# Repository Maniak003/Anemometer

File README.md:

<!DOCTYPE html>
<html lang="en" data-color-mode="auto" data-light-theme="light" data-dark-theme="dark">
  <head>
    <meta charset="utf-8">
  </head>
    <body class="logged-in env-production page-responsive page-blob" style="word-wrap: break-word;">
      <p> UltraSonic Anemometer.<br><b>Temperature instability was found. I'm trying to solve a problem. </p>

      <a href="https://github.com/Maniak003/Anemometer/wiki/Description" rel="nofollow">Description</a>
    </body>
</html>

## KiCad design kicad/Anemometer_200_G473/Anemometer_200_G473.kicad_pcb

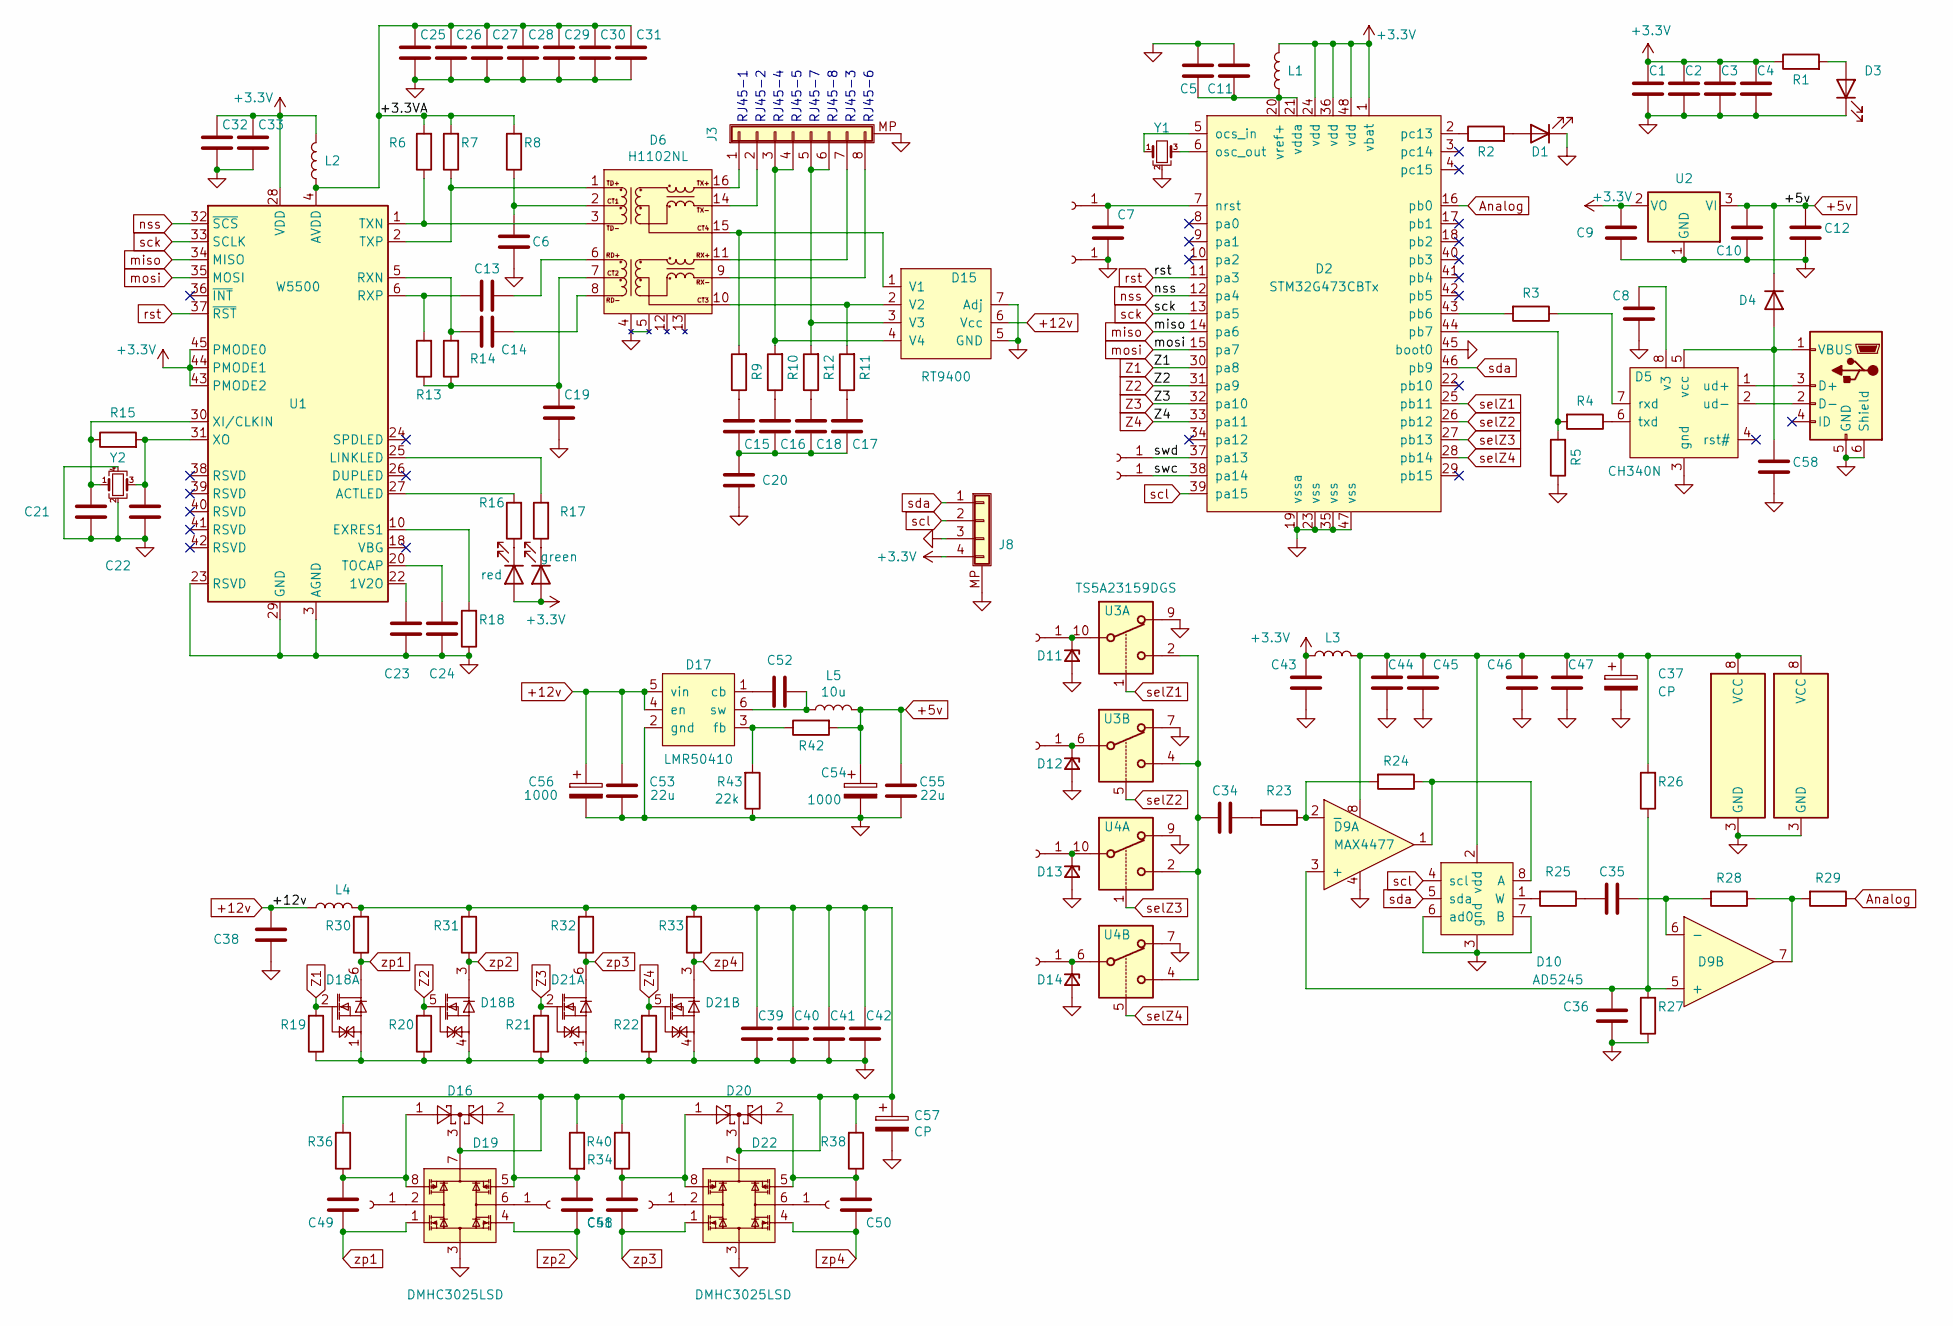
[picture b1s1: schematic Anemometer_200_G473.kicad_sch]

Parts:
C1, C8, C9, C38, C43, C44, C45, C46, C47: C; C_0603_1608Metric
C2, C3, C4, C5, C10, C11, C12, C39, C40, C41, C42, C58: C; C_0805_2012Metric
C6, C25, C26, C27, C28, C29, C30, C31, C32, C33: 22n; C_0402_1005Metric
C7: C; C_0402_1005Metric
C13, C14, C15, C16, C17, C18, C36: 6.8n; C_0402_1005Metric
C19, C23: 10n; C_0402_1005Metric
C20: 10n; C_1206_3216Metric
C21, C22: 10; C_0402_1005Metric
C24, C34, C35: 4.7u; C_0402_1005Metric
C37, C57: CP; CP_EIA-7343-40_Kemet-Y_Pad2.25x2.55mm_HandSolder
C48, C49, C50, C51, C52: 85n; C_0603_1608Metric
C53, C55: 22u; C_0805_2012Metric
C54, C56: 1000; CP_EIA-7343-40_Kemet-Y_Pad2.25x2.55mm_HandSolder
D1, D3: LED; LED_0603_1608Metric
D2: STM32G473CBTx; LQFP-48_7x7mm_P0.5mm
D4: D; D_MiniMELF
D5: CH340N; SOP-8_3.9x4.9mm_P1.27mm
D6: H1102NL; H1102N
D7: red; LED_0603_1608Metric
D8: green; LED_0603_1608Metric
D9: MAX4477; MSOP-8_3x3mm_P0.65mm
D10: AD5245; MSOP-8_3x3mm_P0.65mm
D11, D12, D13, D14: D_Zener_Small; D_SOD-123
D15: RT9400; TR9400
D16, D20: BAT54C; SOT-23
D17: LMR50410; SOT-23-6
D18, D21: DMN5L06DWK-7; SOT-363_SC-70-6
D19, D22: DMHC3025LSD; SO-8_5.3x6.2mm_P1.27mm
J1, J2, J4, J13, J15, J16, J17, J20, J21, J22, J23, J24: Conn_01x01_Female; conn_mini
J3: Conn_01x08_Shielded; JST_GH_BM08B-GHS-TBT_1x08-1MP_P1.25mm_Vertical
J8: Conn_01x04_Shielded; JST_SH_BM04B-SRSS-TB_1x04-1MP_P1.00mm_Vertical
J11: USB_B_Micro; USB_Micro-B_Molex_47346-0001
L1: L; L_0805_2012Metric
L2, L4: 10u; L_0805_2012Metric
L3: 47u; L_0805_2012Metric
L5: 10u; L_Bourns_SRP7028A_7.3x6.6mm
R1, R2, R3, R4, R5, R23, R24, R25, R28, R29: R; R_0603_1608Metric
R6, R7: 49.9; R_0402_1005Metric
R8: 10; R_0402_1005Metric
R9, R10, R11, R12: 75; R_0402_1005Metric
R13, R14: 82; R_0402_1005Metric
R15: 1M; R_0402_1005Metric
R16, R17: 510; R_0402_1005Metric
R18, R26, R27, R34, R36, R38, R40, R42: 12.4k; R_0402_1005Metric
R19, R20, R21, R22: 100k; R_0402_1005Metric
R30, R31, R32, R33: 100; R_0402_1005Metric
R43: 22k; R_0402_1005Metric
U1: W5500; LQFP-48_7x7mm_P0.5mm
U2: NCP1117-3.3; SOT-223-3_TabPin2
U3, U4: TS5A23159DGS; VSSOP-10_3x3mm_P0.5mm
Y1: 16; Resonator_SMD_muRata_CSTxExxV-3Pin_3.0x1.1mm
Y2: 25MHz; Crystal_SMD_SeikoEpson_FA238-4Pin_3.2x2.5mm

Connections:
+3V3: C1.1, C2.1, C3.1, C4.1, C9.1, C32.1, C33.1, C43.1, D2.1 (vbat), D2.24 (vdd), D2.36 (vdd), D2.48 (vdd), D7.2 (A), D8.2 (A), J8.4, L1.2, L2.2, L3.1, R1.1, U1.28 (VDD), U1.43 (PMODE2), U1.44 (PMODE1), U1.45 (PMODE0), U2.2 (VO)
+5v: C10.1, C12.1, C54.1, C55.2, D4.1 (K), L5.2, R42.2, U2.3 (VI)
+12v: C38.1, C53.2, C56.1, D15.6 (Vcc), D17.4 (en), D17.5 (vin), L4.1
/+3.3VA: C25.1, C26.1, C27.1, C28.1, C29.1, C30.1, C31.1, L2.1, R6.2, R7.2, R8.2, U1.4 (AVDD), U1.8 (AVDD), U1.11 (AVDD), U1.15 (AVDD), U1.17 (AVDD), U1.21 (AVDD)
/swc: D2.38 (pa14), J21.1
/swd: D2.37 (pa13), J20.1
Analog: D2.16 (pb0), R29.1
GND: C1.2, C2.2, C3.2, C4.2, C5.2, C6.2, C7.2, C8.2, C9.2, C10.2, C11.2, C12.2, C19.2, C20.2, C21.2, C22.2, C23.2, C24.2, C25.2, C26.2, C27.2, C28.2, C29.2, C30.2, C31.2, C32.2, C33.2, C36.1, C37.2, C38.2, C39.2, C40.2, C41.2, C42.2, C43.2, C44.2, C45.2, C46.2, C47.2, C53.1, C54.2, C55.1, C56.2, C57.2, C58.2, D1.1 (K), D2.19 (vssa), D2.23 (vss), D2.35 (vss), D2.45 (boot0), D2.47 (vss), D3.1 (K), D5.3 (gnd), D6.4, D6.5, D9.4, D10.3 (gnd), D10.6 (ad0), D10.7 (B), D11.2 (A), D12.2 (A), D13.2 (A), D14.2 (A), D15.5 (GND), D15.7 (Adj), D17.2 (gnd), D18.1, D18.4, D19.3, D21.1, D21.4, D22.3, J3.MP (Shield), J4.1, J8.3, J8.MP (Shield), J11.5 (GND), J11.6 (Shield), R5.1, R18.1, R19.1, R20.1, R21.1, R22.1, R27.1, R43.1, U1.3 (AGND), U1.9 (AGND), U1.14 (AGND), U1.16 (AGND), U1.19 (AGND), U1.23 (RSVD), U1.29 (GND), U1.48 (AGND), U2.1 (GND), U3.3 (GND), U3.7, U3.9, U4.3 (GND), U4.7, U4.9, Y1.2, Y2.2, Y2.4
unnamed: C6.1, D6.2, R8.1
unnamed: C7.1, D2.7 (nrst), J1.1
unnamed: C8.1, D5.8 (v3)
unnamed: C5.1, C11.1, D2.20 (vref+), D2.21 (vdda), L1.1
unnamed: C13.1, D6.6
unnamed: C13.2, R13.2, U1.6 (RXP)
unnamed: C14.1, D6.8
unnamed: C14.2, R14.2, U1.5 (RXN)
unnamed: C15.2, R9.1
unnamed: C16.2, R10.1
unnamed: C18.2, R12.1
unnamed: C19.1, D6.7, R13.1, R14.1
unnamed: C15.1, C16.1, C17.1, C18.1, C20.1
unnamed: C21.1, R15.1, U1.30 (XI/CLKIN), Y2.1
unnamed: C22.1, R15.2, U1.31 (XO), Y2.3
unnamed: C23.1, U1.22 (1V2O)
unnamed: C24.1, U1.20 (TOCAP)
unnamed: C34.1, R23.2
unnamed: C34.2, U3.2, U3.4, U4.2, U4.4
unnamed: C35.1, D9.6 (-), R28.2
unnamed: C35.2, R25.1
unnamed: C36.2, D9.3 (+), D9.5 (+), R26.1, R27.2
unnamed: C37.1, C44.1, C45.1, C46.1, C47.1, D9.8, D10.2 (vdd), L3.2, R26.2, U3.8 (VCC), U4.8 (VCC)
unnamed: C39.1, C40.1, C41.1, C42.1, C57.1, D16.3, D19.7, D20.3, D22.7, L4.2, R30.2, R31.2, R32.2, R33.2, R34.1, R36.2, R38.2, R40.2
unnamed: C48.1, D16.2, D19.5, R34.2
unnamed: C49.1, D16.1, D19.8, R36.1
unnamed: C50.1, D20.2, D22.5, R38.1
unnamed: C51.1, D20.1, D22.8, R40.1
unnamed: C52.1, D17.6 (sw), L5.1
unnamed: C52.2, D17.1 (cb)
unnamed: D1.2 (A), R2.2
unnamed: D2.2 (pc13), R2.1
unnamed: D2.5 (ocs_in), Y1.1
unnamed: D2.6 (osc_out), Y1.3
unnamed: D2.43 (pb6), R3.2
unnamed: D2.44 (pb7), R4.2, R5.2
unnamed: D3.2 (A), R1.2
unnamed: C58.1, D4.2 (A), D5.5 (vcc), J11.1 (VBUS)
unnamed: D5.1 (ud+), J11.3 (D+)
unnamed: D5.2 (ud-), J11.2 (D-)
unnamed: D5.6 (txd), R4.1
unnamed: D5.7 (rxd), R3.1
unnamed: D6.9, J3.8
unnamed: D6.11, J3.7
unnamed: D6.14, J3.2
unnamed: D6.16, J3.1
unnamed: D9.2 (-), R23.1, R24.2
unnamed: D9.7, R28.1, R29.2
unnamed: D10.1 (W), R25.2
unnamed: D9.1, D10.8 (A), R24.1
unnamed: D11.1 (K), J17.1, U3.10
unnamed: D12.1 (K), J22.1, U3.6
unnamed: D13.1 (K), J23.1, U4.10
unnamed: D14.1 (K), J24.1, U4.6
unnamed: D6.15, D15.1 (V1), R9.2
unnamed: D6.10, D15.2 (V2), R11.2
unnamed: D15.3 (V3), J3.5, J3.6, R12.2
unnamed: D15.4 (V4), J3.3, J3.4, R10.2
unnamed: D17.3 (fb), R42.1, R43.2
unnamed: D19.6, J2.1
unnamed: D22.2, J13.1
unnamed: D19.2, J15.1
unnamed: D22.6, J16.1
unnamed: D6.3, R6.1, U1.1 (TXN)
unnamed: D6.1, R7.1, U1.2 (TXP)
unnamed: C17.2, R11.1
unnamed: D7.1 (K), R16.1
unnamed: D8.1 (K), R17.1
unnamed: R18.2, U1.10 (EXRES1)
unnamed: R17.2, U1.25 (LINKLED)
unnamed: R16.2, U1.27 (ACTLED)
Z1: D2.30 (pa8), D18.2, R19.2
Z2: D2.31 (pa9), D18.5, R20.2
Z3: D2.32 (pa10), D21.2, R21.2
Z4: D2.33 (pa11), D21.5, R22.2
miso: D2.14 (pa6), U1.34 (MISO)
mosi: D2.15 (pa7), U1.35 (MOSI)
nss: D2.12 (pa4), U1.32 (~SCS)
rst: D2.11 (pa3), U1.37 (~RST)
sck: D2.13 (pa5), U1.33 (SCLK)
scl: D2.39 (pa15), D10.4 (scl), J8.2
sda: D2.46 (pb9), D10.5 (sda), J8.1
selZ1: D2.25 (pb11), U3.1
selZ2: D2.26 (pb12), U3.5
selZ3: D2.27 (pb13), U4.1
selZ4: D2.28 (pb14), U4.5
zp1: C49.2, D18.6, D19.1, R30.1
zp2: C48.2, D18.3, D19.4, R31.1
zp3: C51.2, D21.6, D22.1, R32.1
zp4: C50.2, D21.3, D22.4, R33.1

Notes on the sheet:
RJ45-1
RJ45-3
RJ45-2
RJ45-6
RJ45-8
RJ45-5
RJ45-4
RJ45-7

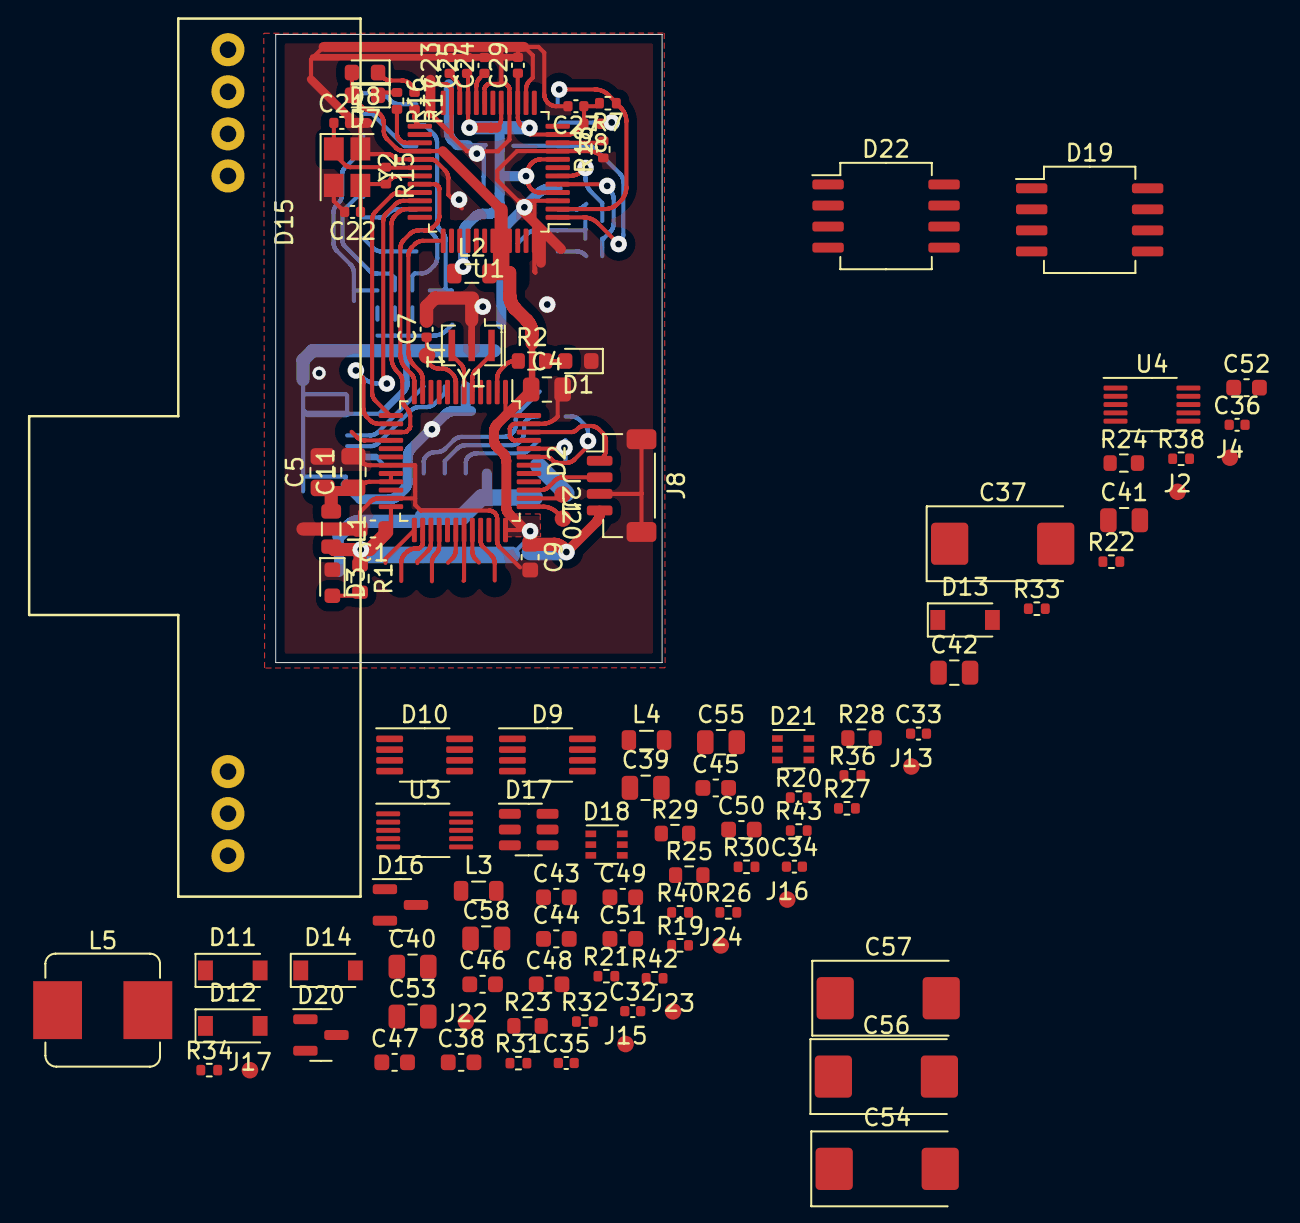
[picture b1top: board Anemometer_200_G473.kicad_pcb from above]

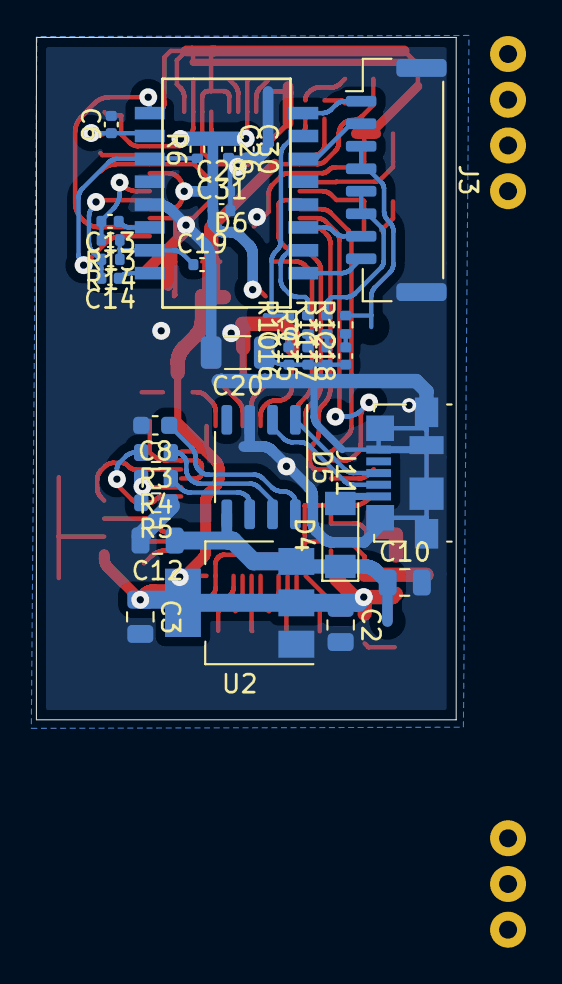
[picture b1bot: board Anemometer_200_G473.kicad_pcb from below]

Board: 2 copper layers, 23.3 x 37.9 mm, 145 parts (34 on the bottom side), 98 nets.

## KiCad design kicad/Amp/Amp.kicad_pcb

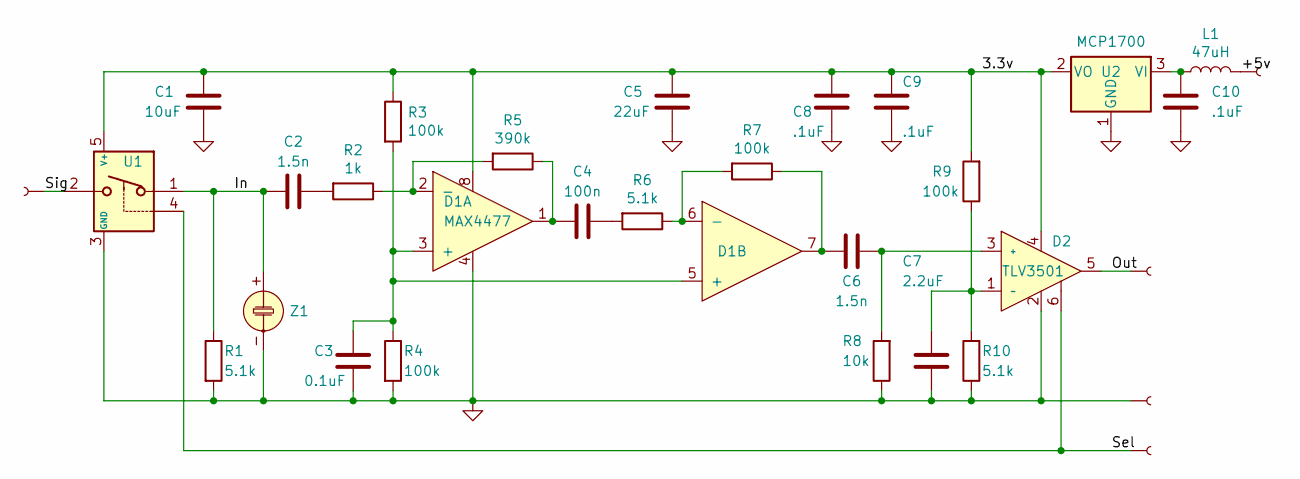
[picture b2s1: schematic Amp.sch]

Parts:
C1: 10uF; C_0603_1608Metric
C2, C6: 1.5n; C_0402_1005Metric
C3: 0.1uF; C_0402_1005Metric
C4: 100n; C_0402_1005Metric
C5: 22uF; C_0805_2012Metric
C7: 2.2uF; C_0402_1005Metric
C8, C9, C10: .1uF; C_0603_1608Metric
D1: MAX4477; MSOP-8_3x3mm_P0.65mm
D2: TLV3501; SOT-23-6
J1, J2, J3, J4, J5: Conn; SMD-CONN
L1: 47uH; L_0805_2012Metric
R1, R6, R10: 5.1k; R_0402_1005Metric
R2: 1k; R_0402_1005Metric
R3, R4, R7, R9: 100k; R_0402_1005Metric
R5: 390k; R_0402_1005Metric
R8: 10k; R_0402_1005Metric
U1: TS5A3166DBVR; SOT-23-5
U2: MCP1700; SOT-23
Z1: MCUSD18A40B12RS

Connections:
/3.3v: C1.1, C5.1, C8.1, C9.1, D1.8, D2.4, R3.1, R9.2, U1.5 (V+), U2.2 (VO)
/+5v: J5.1, L1.2
/In: C2.2, R1.1, U1.1, Z1.+
/Out: D2.5, J2.1
/Sel: D2.6, J4.1, U1.4
/Sig: J1.1, U1.2
GND: C1.2, C3.2, C5.2, C7.2, C8.2, C9.2, C10.2, D1.4, D2.2, J3.1, R1.2, R4.2, R8.1, R10.1, U1.3 (GND), U2.1 (GND), Z1.-
unnamed: C2.1, R2.2
unnamed: C3.1, D1.3 (+), D1.5 (+), R3.2, R4.1
unnamed: C4.1, R6.2
unnamed: C4.2, D1.1, R5.1
unnamed: C6.1, D2.3 (+), R8.2
unnamed: C6.2, D1.7, R7.1
unnamed: C7.1, D2.1 (-), R9.1, R10.2
unnamed: C10.1, L1.1, U2.3 (VI)
unnamed: D1.2 (-), R2.1, R5.2
unnamed: D1.6 (-), R6.1, R7.2

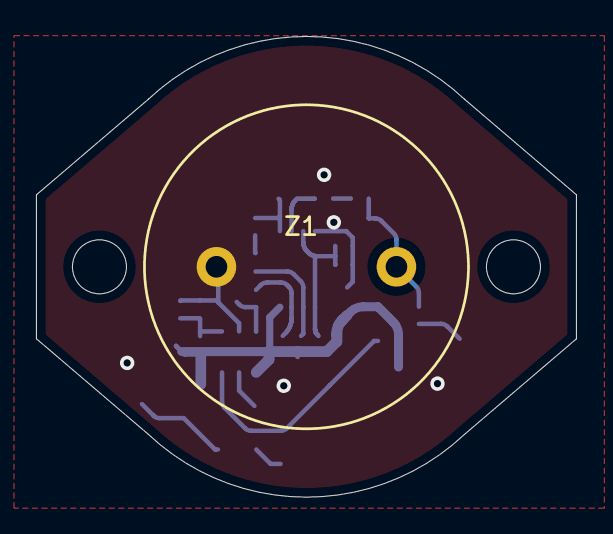
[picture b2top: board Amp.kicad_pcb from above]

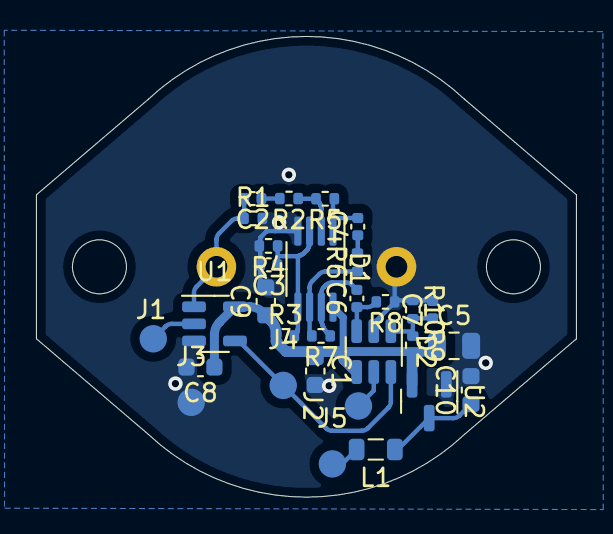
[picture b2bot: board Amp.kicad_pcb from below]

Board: 2 copper layers, 30.0 x 25.6 mm, 31 parts (30 on the bottom side), 17 nets.

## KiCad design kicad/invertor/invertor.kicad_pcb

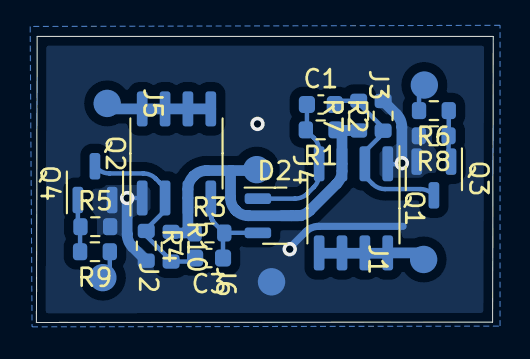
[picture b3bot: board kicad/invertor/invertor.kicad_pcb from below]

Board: 2 copper layers, 25.4 x 15.9 mm, 23 parts (23 on the bottom side), 12 nets.

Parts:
C1, C3: 82nF; C_0603_1608Metric
D2: BAT54C; SOT-23
J1, J2, J3, J4, J5, J6: Conn; SMD-CONN
Q1, Q2: IRF7343PBF; SOIC-8_3.9x4.9mm_P1.27mm
Q3, Q4: IRLML6344; SOT-23
R1, R2, R3, R4, R5, R8: 100k; R_0603_1608Metric
R6, R9: 10; R_0603_1608Metric
R7, R10: 100; R_0603_1608Metric

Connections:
/+12v: D2.3, J4.1, Q1.3 (1), Q2.3 (1), R1.1, R3.1, R7.1, R10.1
/Z1: J2.1, R9.1
/Z2: J3.1, R6.2
GND: J6.1, Q1.1 (S), Q2.1 (S), Q3.2 (S), Q4.2 (S), R2.2, R4.2, R5.2, R8.2
unnamed: C1.1, D2.1, Q1.4 (G), R1.2
unnamed: C1.2, Q1.2 (G), Q3.3 (D), R2.1, R7.2
unnamed: C3.1, D2.2, Q2.4 (G), R3.2
unnamed: C3.2, Q2.2 (G), Q4.3 (D), R4.1, R10.2
unnamed: J1.1, Q1.5 (D), Q1.6 (D), Q1.7 (D), Q1.8 (D)
unnamed: J5.1, Q2.5 (D), Q2.6 (D), Q2.7 (D), Q2.8 (D)
unnamed: Q3.1 (G), R6.1, R8.1
unnamed: Q4.1 (G), R5.1, R9.2

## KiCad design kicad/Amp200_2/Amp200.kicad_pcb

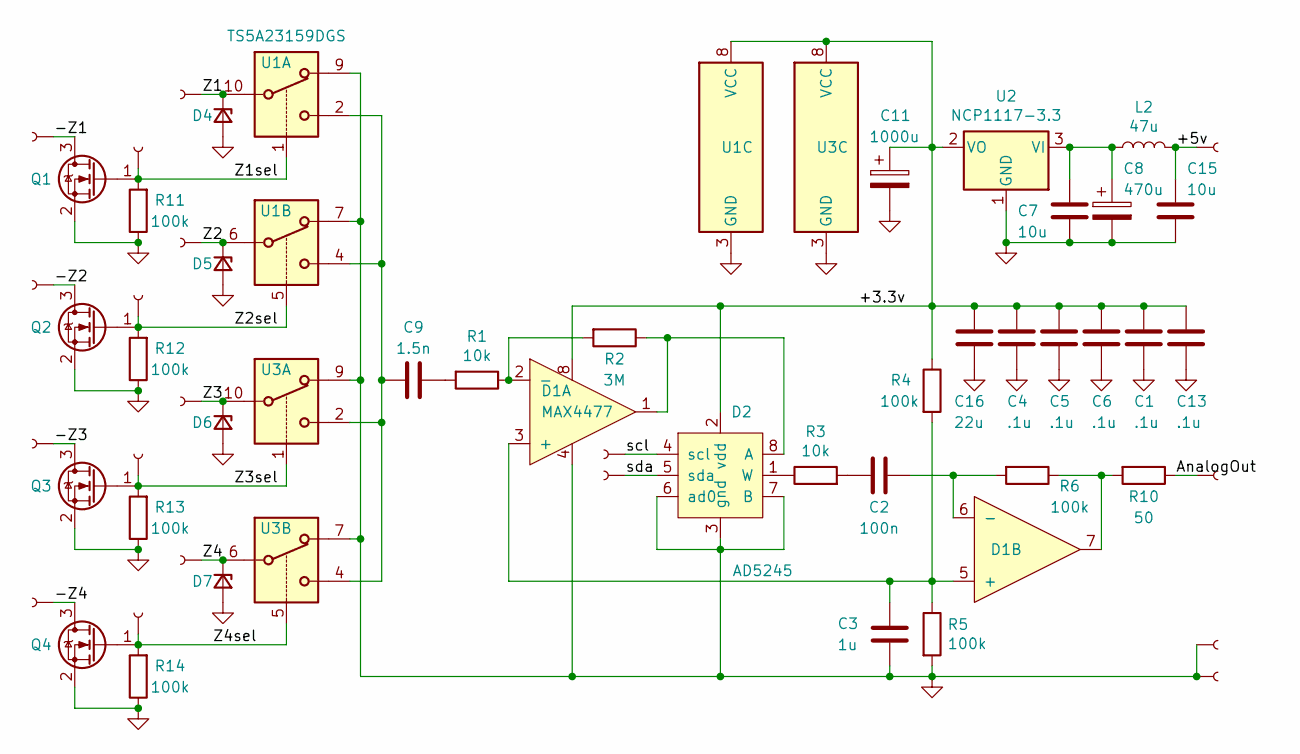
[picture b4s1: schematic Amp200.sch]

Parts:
C1, C4, C5, C6, C13: .1u; C_0805_2012Metric
C2: 100n; C_0603_1608Metric
C3: 1u; C_0603_1608Metric
C7, C15: 10u; C_0805_2012Metric
C8: 470u; CP_EIA-6032-28_Kemet-C
C9: 1.5n; C_0603_1608Metric
C11: 1000u; CP_EIA-6032-28_Kemet-C
C16: 22u; C_0805_2012Metric
D1: MAX4477; MSOP-8_3x3mm_P0.65mm
D2: AD5245; SOT-23-8
D4, D5, D6, D7: BZ55C2V7; D_MiniMELF
J1, J2, J3, J4, J5, J7, J8, J9, J10, J11, J12, J13, J14, J15, J16, J17, J18, J19: Conn; SMD-CONN
L2: 47u; L_0805_2012Metric
Q1, Q2, Q3, Q4: Q_NMOS_GSD; SOT-23
R1, R3: 10k; R_0603_1608Metric
R2: 3M; R_0603_1608Metric
R4, R5, R6, R11, R12, R13, R14: 100k; R_0603_1608Metric
R10: 50; R_0603_1608Metric
U1, U3: TS5A23159DGS; VSSOP-10_3x3mm_P0.5mm
U2: NCP1117-3.3; SOT-223-3_TabPin2

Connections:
/+3.3v: C1.1, C4.1, C5.1, C6.1, C11.1, C13.1, C16.1, D1.8, D2.2 (vdd), R4.1, U1.8 (VCC), U2.2 (VO), U3.8 (VCC)
/+5v: C15.1, J9.1, L2.2
/-Z1: J4.1, Q1.3 (D)
/-Z2: J17.1, Q2.3 (D)
/-Z3: J14.1, Q3.3 (D)
/-Z4: J18.1, Q4.3 (D)
/AnalogOut: J5.1, R10.1
/Z1: D4.1 (K), J1.1, U1.10
/Z1sel: J7.1, Q1.1 (G), R11.2, U1.1
/Z2: D5.1 (K), J11.1, U1.6
/Z2sel: J12.1, Q2.1 (G), R12.2, U1.5
/Z3: D6.1 (K), J13.1, U3.10
/Z3sel: J19.1, Q3.1 (G), R13.2, U3.1
/Z4: D7.1 (K), J15.1, U3.6
/Z4sel: J16.1, Q4.1 (G), R14.2, U3.5
/scl: D2.4 (scl), J2.1
/sda: D2.5 (sda), J3.1
GND: C1.2, C3.2, C4.2, C5.2, C6.2, C7.2, C8.2, C11.2, C13.2, C15.2, C16.2, D1.4, D2.3 (gnd), D2.6 (ad0), D2.7 (B), D4.2 (A), D5.2 (A), D6.2 (A), D7.2 (A), J8.1, J10.1, Q1.2 (S), Q2.2 (S), Q3.2 (S), Q4.2 (S), R5.2, R11.1, R12.1, R13.1, R14.1, U1.3 (GND), U1.7, U1.9, U2.1 (GND), U3.3 (GND), U3.7, U3.9
unnamed: C2.1, D1.6 (-), R6.2
unnamed: C2.2, R3.2
unnamed: C3.1, D1.3 (+), D1.5 (+), R4.2, R5.1
unnamed: C7.1, C8.1, L2.1, U2.3 (VI)
unnamed: C9.1, R1.2
unnamed: C9.2, U1.2, U1.4, U3.2, U3.4
unnamed: D1.1, D2.8 (A), R2.1
unnamed: D1.2 (-), R1.1, R2.2
unnamed: D1.7, R6.1, R10.2
unnamed: D2.1 (W), R3.1

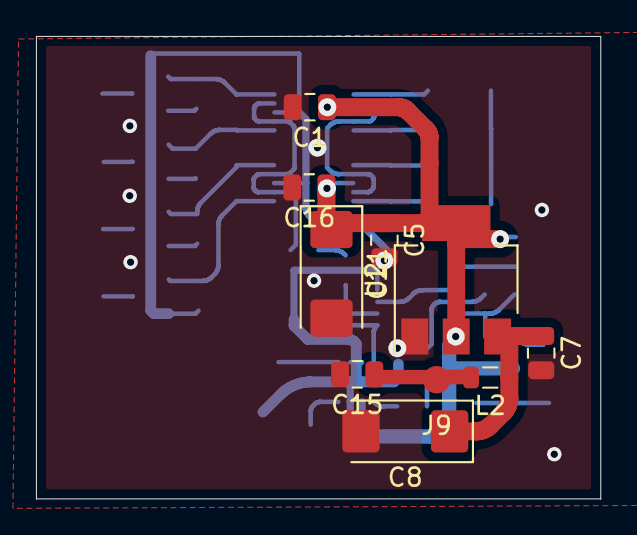
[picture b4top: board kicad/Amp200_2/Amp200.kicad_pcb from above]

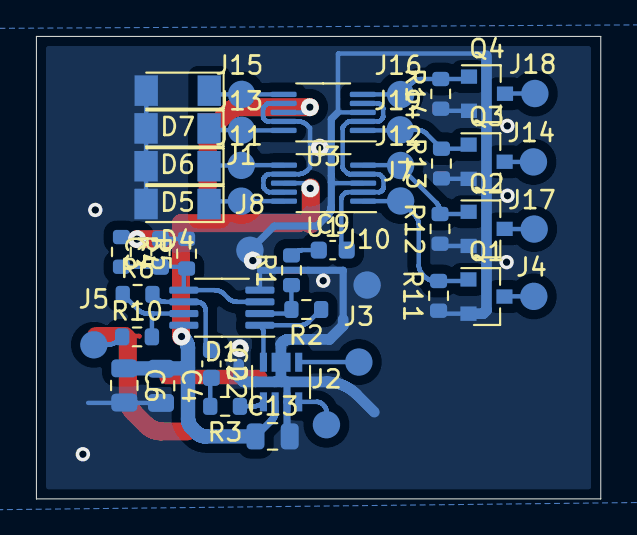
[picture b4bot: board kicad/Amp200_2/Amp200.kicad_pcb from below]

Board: 2 copper layers, 31.4 x 25.7 mm, 56 parts (46 on the bottom side), 28 nets.

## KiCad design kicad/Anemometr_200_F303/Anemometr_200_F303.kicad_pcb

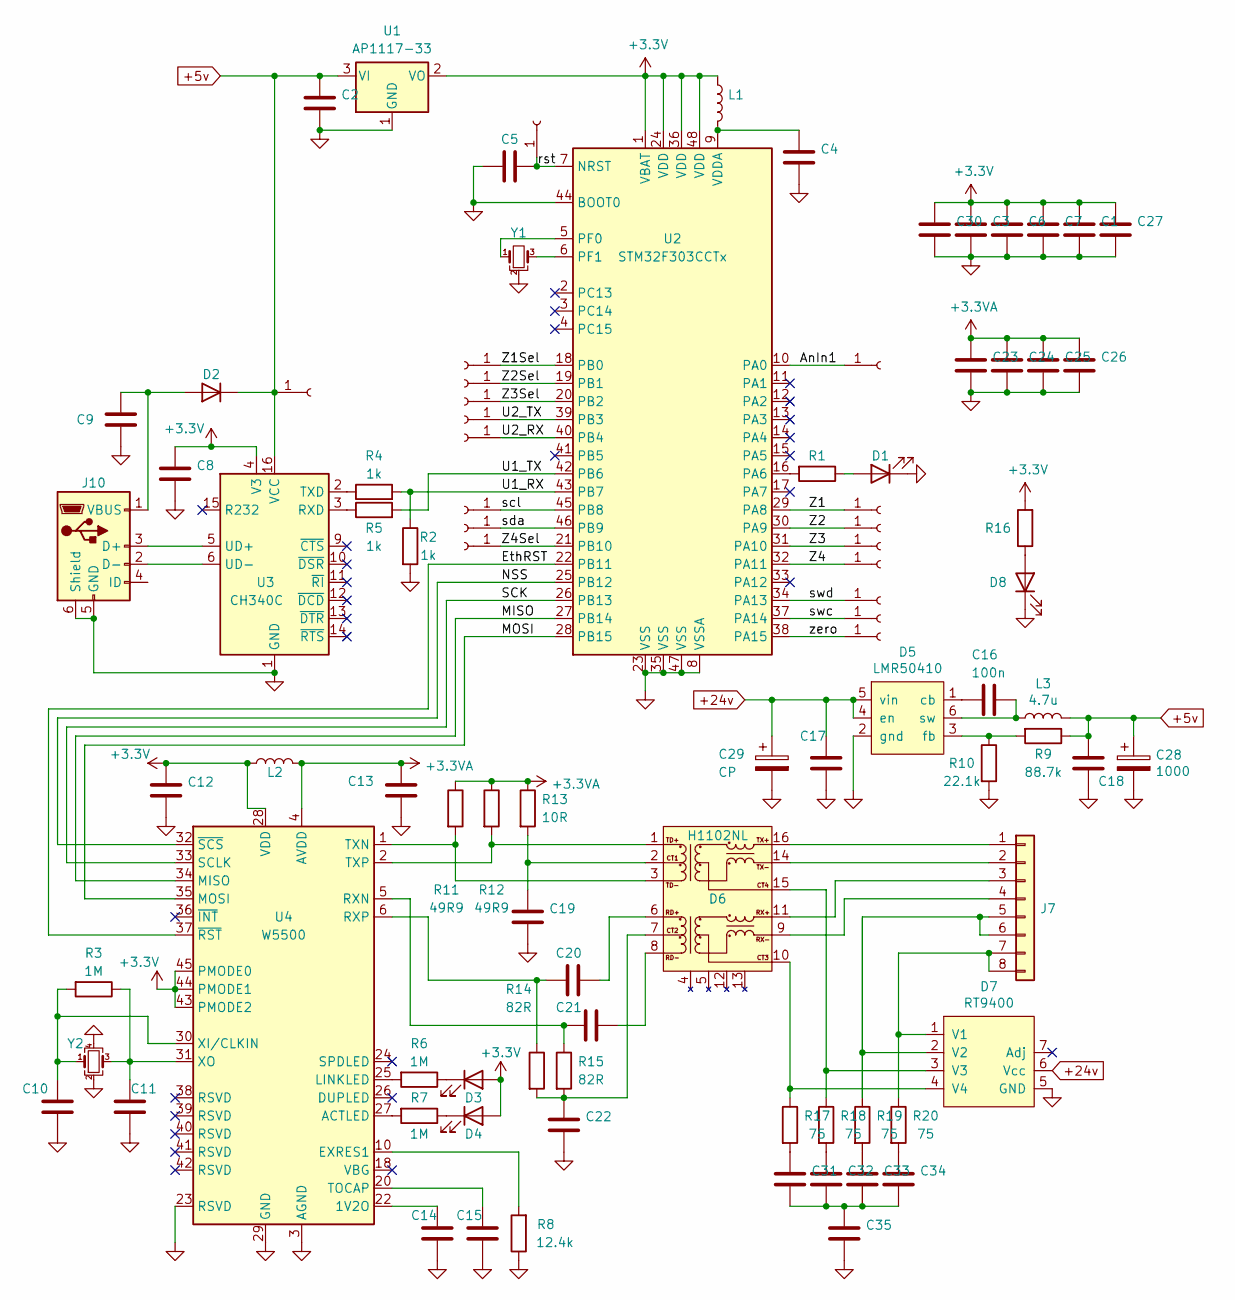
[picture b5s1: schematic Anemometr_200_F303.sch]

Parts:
C1, C2, C3, C4, C5, C6, C7, C8, C9, C12: C; C_0603_1608Metric
C10, C11, C13, C23, C24, C25, C26, C27: C; C_0402_1005Metric
C14, C22: 10n; C_0402_1005Metric
C15: 4.7u; C_0402_1005Metric
C16: 100n; C_0805_2012Metric
C17, C18, C30: C; C_0805_2012Metric
C19: 22n; C_0402_1005Metric
C20, C21, C31, C32, C33, C34: 6.8n; C_0402_1005Metric
C28: 1000; CP_EIA-7343-15_Kemet-W
C29: CP; CP_EIA-7343-15_Kemet-W
C35: 6.8n; C_1206_3216Metric
D1, D3, D4, D8: LED; LED_0603_1608Metric
D2: D; D_SOD-123
D5: LMR50410; SOT-23-6
D6: H1102NL; H1102N
D7: RT9400; TR9400
J1, J2, J3, J4, J5, J6, J11, J12, J13, J14, J15, J16, J17, J19, J23, J25, J26, J27: Conn_01x01_Female; mini_conn
J7: Conn_01x08; JST_SH_BM08B-SRSS-TB_1x08-1MP_P1.00mm_Vertical
J10: USB_B_Micro; USB_Micro-B_Molex_47346-0001
L1, L2: L; L_0805_2012Metric
L3: 4.7u; L_Abracon_ASPI-0630LR
R1: R; R_0603_1608Metric
R2, R4, R5, R16: 1k; R_0603_1608Metric
R3, R6, R7: 1M; R_0402_1005Metric
R8: 12.4k; R_0402_1005Metric
R9: 88.7k; R_0603_1608Metric
R10: 22.1k; R_0603_1608Metric
R11, R12: 49R9; R_0402_1005Metric
R13: 10R; R_0402_1005Metric
R14, R15: 82R; R_0402_1005Metric
R17, R18, R19, R20: 75; R_0402_1005Metric
U1: AP1117-33; SOT-223-3_TabPin2
U2: STM32F303CCTx; LQFP-48_7x7mm_P0.5mm
U3: CH340C; SOIC-16_3.9x9.9mm_P1.27mm
U4: W5500; LQFP-48_7x7mm_P0.5mm
Y1: 16MHz; Resonator_SMD_muRata_CSTxExxV-3Pin_3.0x1.1mm
Y2: Crystal_GND24_Small; Crystal_SMD_SeikoEpson_FA238-4Pin_3.2x2.5mm

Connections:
+3.3VA: C13.1, C23.1, C24.1, C25.1, C26.1, L2.2, R11.1, R12.1, R13.1, U4.4 (AVDD), U4.8 (AVDD), U4.11 (AVDD), U4.15 (AVDD), U4.17 (AVDD), U4.21 (AVDD)
+3V3: C1.1, C3.1, C6.1, C7.1, C8.1, C12.1, C27.1, C30.1, D3.2 (A), D4.2 (A), L1.1, L2.1, R16.2, U1.2 (VO), U2.1 (VBAT), U2.24 (VDD), U2.36 (VDD), U2.48 (VDD), U3.4 (V3), U4.28 (VDD), U4.43 (PMODE2), U4.44 (PMODE1), U4.45 (PMODE0)
+5v: C2.1, C18.1, C28.1, D2.1 (K), J1.1, L3.2, R9.1, U1.3 (VI), U3.16 (VCC)
+24v: C17.1, C29.1, D5.4 (en), D5.5 (vin), D7.6 (Vcc)
/AnIn1: J3.1, U2.10 (PA0)
/EthRST: U2.22 (PB11), U4.37 (~RST)
/MISO: U2.27 (PB14), U4.34 (MISO)
/MOSI: U2.28 (PB15), U4.35 (MOSI)
/NSS: U2.25 (PB12), U4.32 (~SCS)
/SCK: U2.26 (PB13), U4.33 (SCLK)
/U1_RX: R2.1, R4.2, U2.43 (PB7)
/U1_TX: R5.2, U2.42 (PB6)
/U2_RX: J25.1, U2.40 (PB4)
/U2_TX: J26.1, U2.39 (PB3)
/Z1: J13.1, U2.29 (PA8)
/Z1Sel: J2.1, U2.18 (PB0)
/Z2: J15.1, U2.30 (PA9)
/Z2Sel: J4.1, U2.19 (PB1)
/Z3: J17.1, U2.31 (PA10)
/Z3Sel: J6.1, U2.20 (PB2)
/Z4: J19.1, U2.32 (PA11)
/Z4Sel: J16.1, U2.21 (PB10)
/rst: C5.1, J11.1, U2.7 (NRST)
/scl: J12.1, U2.45 (PB8)
/sda: J14.1, U2.46 (PB9)
/swc: J23.1, U2.37 (PA14)
/swd: J27.1, U2.34 (PA13)
/zero: J5.1, U2.38 (PA15)
GND: C1.2, C2.2, C3.2, C4.2, C5.2, C6.2, C7.2, C8.2, C9.2, C10.2, C11.2, C12.2, C13.2, C14.2, C15.2, C17.2, C18.2, C19.2, C22.2, C23.2, C24.2, C25.2, C26.2, C27.2, C28.2, C29.2, C30.2, C35.2, D1.1 (K), D5.2 (gnd), D7.5 (GND), D8.1 (K), J10.5 (GND), J10.6 (Shield), R2.2, R8.1, R10.2, U1.1 (GND), U2.8 (VSSA), U2.23 (VSS), U2.35 (VSS), U2.44 (BOOT0), U2.47 (VSS), U3.1 (GND), U4.3 (AGND), U4.9 (AGND), U4.14 (AGND), U4.16 (AGND), U4.19 (AGND), U4.23 (RSVD), U4.29 (GND), U4.48 (AGND), Y1.2, Y2.2, Y2.4
unnamed: C4.1, L1.2, U2.9 (VDDA)
unnamed: C9.1, D2.2 (A), J10.1 (VBUS)
unnamed: C10.1, R3.2, U4.30 (XI/CLKIN), Y2.1
unnamed: C11.1, R3.1, U4.31 (XO), Y2.3
unnamed: C14.1, U4.22 (1V2O)
unnamed: C15.1, U4.20 (TOCAP)
unnamed: C16.1, D5.6 (sw), L3.1
unnamed: C16.2, D5.1 (cb)
unnamed: C19.1, D6.2, R13.2
unnamed: C20.1, D6.6
unnamed: C20.2, R14.1, U4.6 (RXP)
unnamed: C21.1, D6.8
unnamed: C21.2, R15.1, U4.5 (RXN)
unnamed: C22.1, D6.7, R14.2, R15.2
unnamed: C31.1, R17.2
unnamed: C31.2, C32.2, C33.2, C34.2, C35.1
unnamed: C32.1, R18.2
unnamed: C33.1, R19.2
unnamed: C34.1, R20.2
unnamed: D1.2 (A), R1.1
unnamed: D3.1 (K), R6.1
unnamed: D4.1 (K), R7.1
unnamed: D5.3 (fb), R9.2, R10.1
unnamed: D6.1, R12.2, U4.2 (TXP)
unnamed: D6.3, R11.2, U4.1 (TXN)
unnamed: D6.9, J7.4
unnamed: D6.10, D7.4 (V4), R17.1
unnamed: D6.11, J7.3
unnamed: D6.14, J7.2
unnamed: D6.15, D7.3 (V3), R18.1
unnamed: D6.16, J7.1
unnamed: D7.1 (V1), J7.7, J7.8, R20.1
unnamed: D7.2 (V2), J7.5, J7.6, R19.1
unnamed: D8.2 (A), R16.1
unnamed: J10.2 (D-), U3.6 (UD-)
unnamed: J10.3 (D+), U3.5 (UD+)
unnamed: R1.2, U2.16 (PA6)
unnamed: R4.1, U3.2 (TXD)
unnamed: R5.1, U3.3 (RXD)
unnamed: R6.2, U4.25 (LINKLED)
unnamed: R7.2, U4.27 (ACTLED)
unnamed: R8.2, U4.10 (EXRES1)
unnamed: U2.5 (PF0), Y1.1
unnamed: U2.6 (PF1), Y1.3

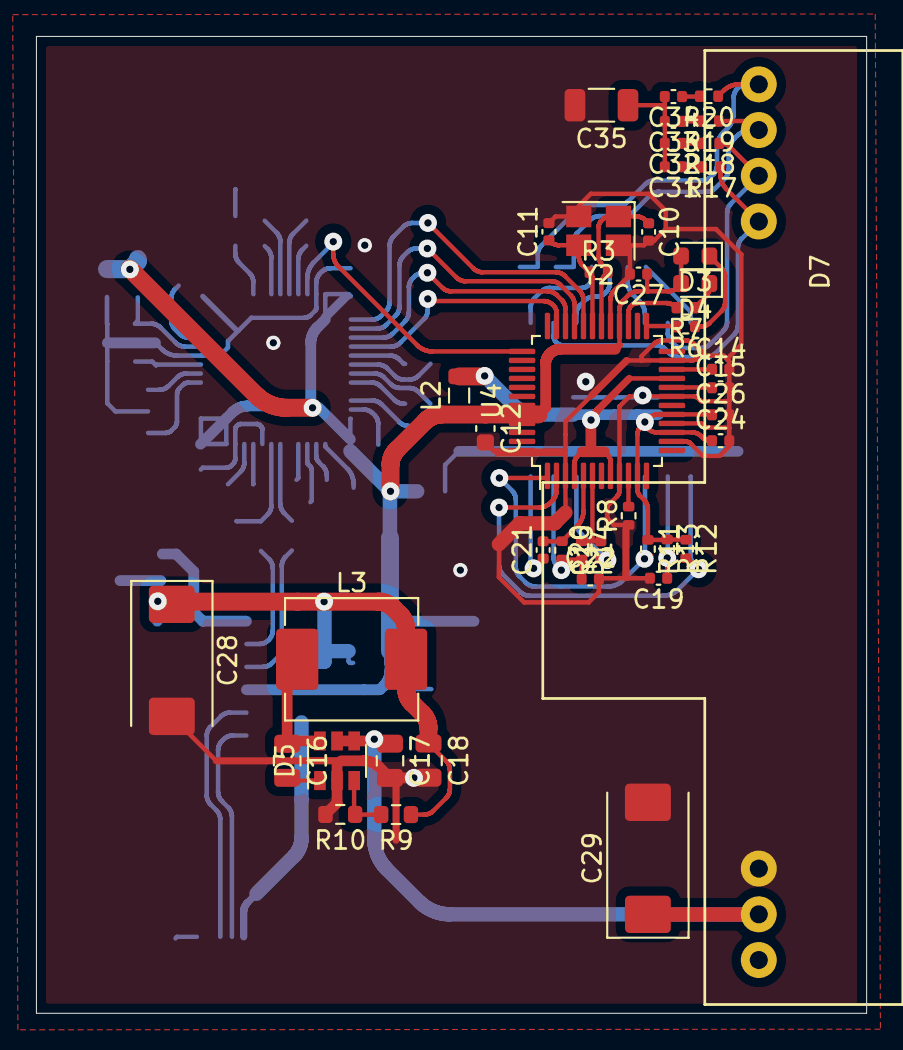
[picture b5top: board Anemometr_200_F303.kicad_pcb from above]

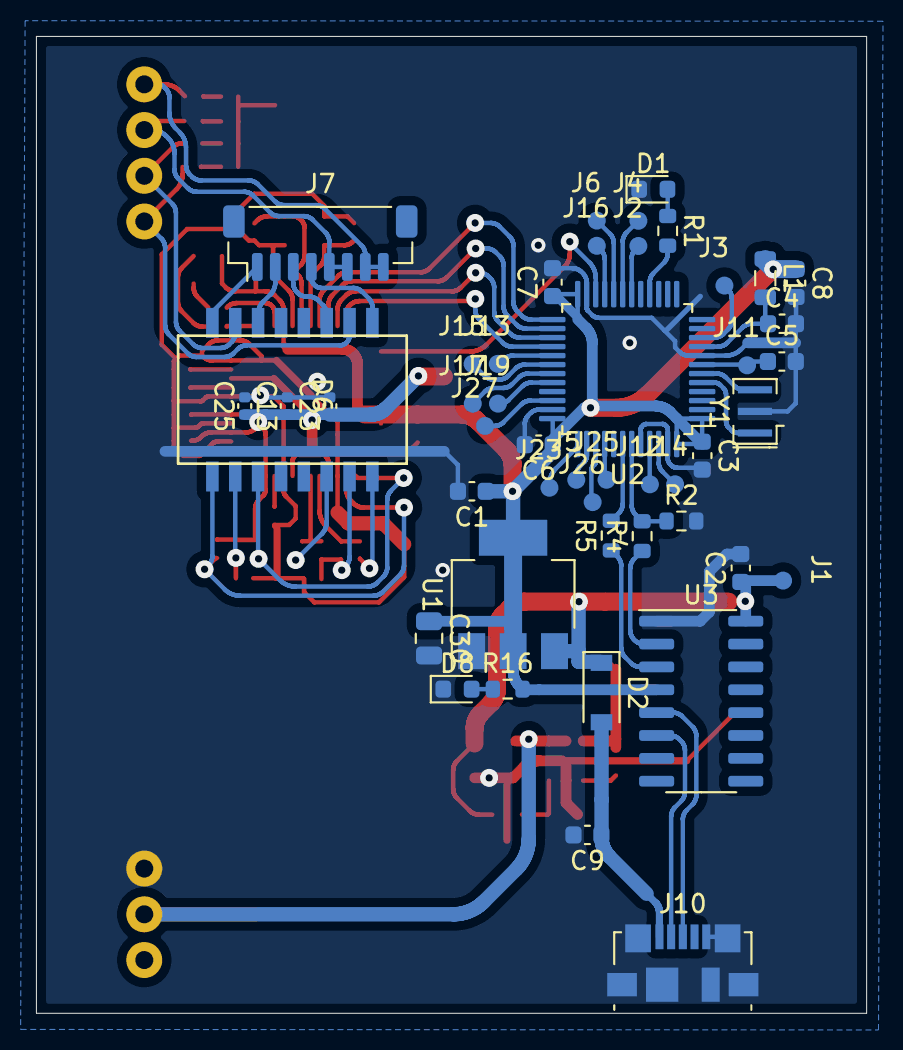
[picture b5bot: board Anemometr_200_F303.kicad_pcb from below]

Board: 2 copper layers, 46.1 x 54.3 mm, 92 parts (47 on the bottom side), 73 nets.

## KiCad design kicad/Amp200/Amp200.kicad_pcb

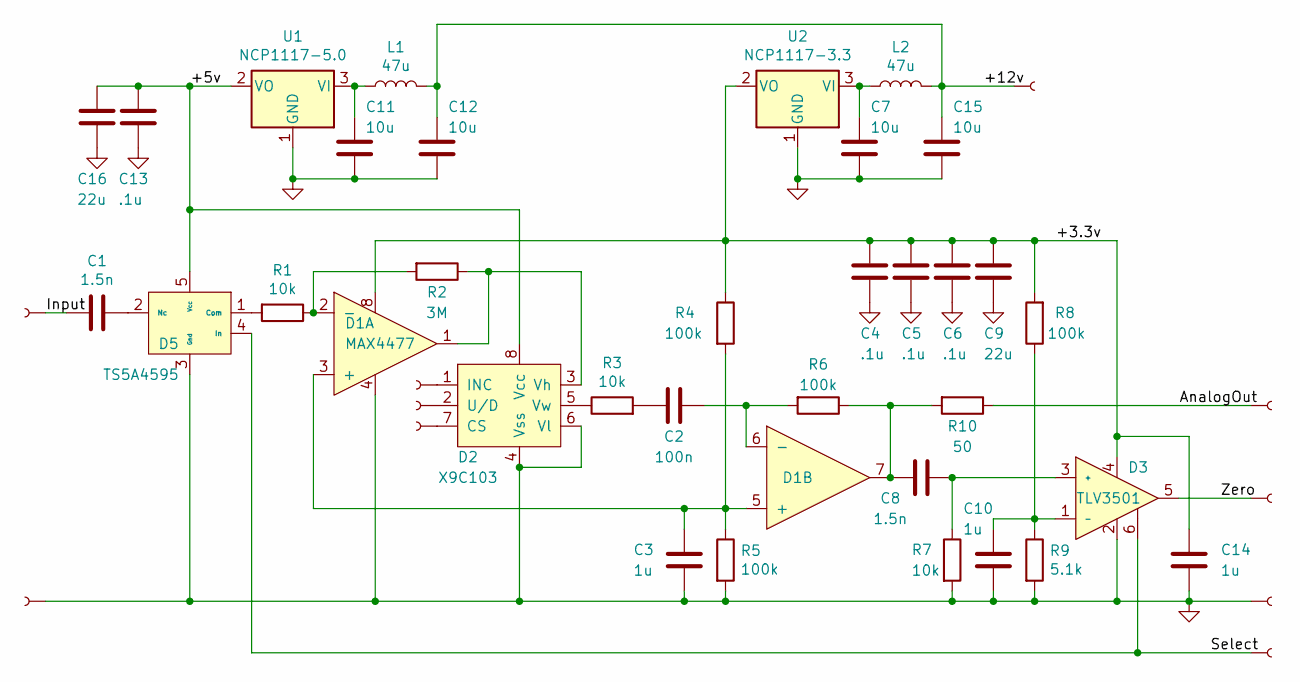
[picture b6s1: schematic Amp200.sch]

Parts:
C1, C8: 1.5n; C_0603_1608Metric
C2: 100n; C_0603_1608Metric
C3, C10: 1u; C_0603_1608Metric
C4, C5, C6, C13: .1u; C_0805_2012Metric
C7, C11, C12, C15: 10u; C_0805_2012Metric
C9, C16: 22u; C_0805_2012Metric
C14: 1u; C_0805_2012Metric
D1: MAX4477; MSOP-8_3x3mm_P0.65mm
D2: X9C103; SOIC-8_3.9x4.9mm_P1.27mm
D3: TLV3501; SOT-23-6
D5: TS5A4595; SOT-23-5
J1, J2, J3, J4, J5, J6, J7, J8, J9, J10: Conn; SMD-CONN
L1, L2: 47u; L_0805_2012Metric
R1, R3, R7: 10k; R_0603_1608Metric
R2: 3M; R_0603_1608Metric
R4, R5, R6, R8: 100k; R_0603_1608Metric
R9: 5.1k; R_0603_1608Metric
R10: 50; R_0603_1608Metric
U1: NCP1117-5.0; SOT-223-3_TabPin2
U2: NCP1117-3.3; SOT-223-3_TabPin2

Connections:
/+3.3v: C4.1, C5.1, C6.1, C9.1, C14.1, D1.8, D3.4, R4.1, R8.2, U2.2 (VO)
/+5v: C13.1, C16.1, D2.8 (Vcc), D5.5 (Vcc), U1.2 (VO)
/+12v: C12.1, C15.1, J9.1, L1.2, L2.2
/AnalogOut: J5.1, R10.1
/Input: C1.2, J1.1
/Select: D3.6, D5.4 (In), J7.1
/Zero: D3.5, J6.1
GND: C3.2, C4.2, C5.2, C6.2, C7.2, C9.2, C10.2, C11.2, C12.2, C13.2, C14.2, C15.2, C16.2, D1.4, D2.4 (Vss), D2.6 (Vl), D3.2, D5.3 (Gnd), J8.1, J10.1, R5.2, R7.2, R9.2, U1.1 (GND), U2.1 (GND)
unnamed: C1.1, D5.2 (Nc)
unnamed: C2.1, D1.6 (-), R6.2
unnamed: C2.2, R3.2
unnamed: C3.1, D1.3 (+), D1.5 (+), R4.2, R5.1
unnamed: C7.1, L2.1, U2.3 (VI)
unnamed: C8.1, D3.3 (+), R7.1
unnamed: C8.2, D1.7, R6.1, R10.2
unnamed: C10.1, D3.1 (-), R8.1, R9.1
unnamed: C11.1, L1.1, U1.3 (VI)
unnamed: D1.1, D2.3 (Vh), R2.1
unnamed: D1.2 (-), R1.1, R2.2
unnamed: D2.1 (INC), J2.1
unnamed: D2.2 (U/D), J3.1
unnamed: D2.5 (Vw), R3.1
unnamed: D2.7 (CS), J4.1
unnamed: D5.1 (Com), R1.2
